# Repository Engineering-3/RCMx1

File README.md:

RCMx1
========================

This is an interface board for the RCM Control Stack that accommodates inputs (sensors) and outputs (motors, servos, LEDs) and communication through UART, SPI and I2C. Please see [Engineering3](http://engineering3.org/) for more information on the complete RCM Control Stack project.

Repository Contents
-------------------

* **/board** Eagle schematic/board files, gerbers, BOM
* **/firmware** Microcontroller firmware build files

Version History
---------------
* [RCMx1 Board v03](https://github.com/Engineering-3/RCMx1/tree/master/board/RCMx1_v03) First public hardware version - version 3 
* [RCMx1 Firmware v07](https://github.com/Engineering-3/RCMx1/tree/master/firmware) First public firmware version - version 7

License Information
-------------------
Hardware is released under [Solderpad Hardware License v0.51](http://solderpad.org/licenses/SHL-0.51/).
Firmware is released under [GNU GPL v2](http://www.gnu.org/licenses/old-licenses/gpl-2.0.html).
Distributed as-is; no warranty is given.

Getting Started Help
--------------------
Follow the [RCMx1 User Guide](https://github.com/Engineering-3/RCMx1/blob/master/firmware/docs/RCMx1%20User%20Guide.doc) here in the repo.

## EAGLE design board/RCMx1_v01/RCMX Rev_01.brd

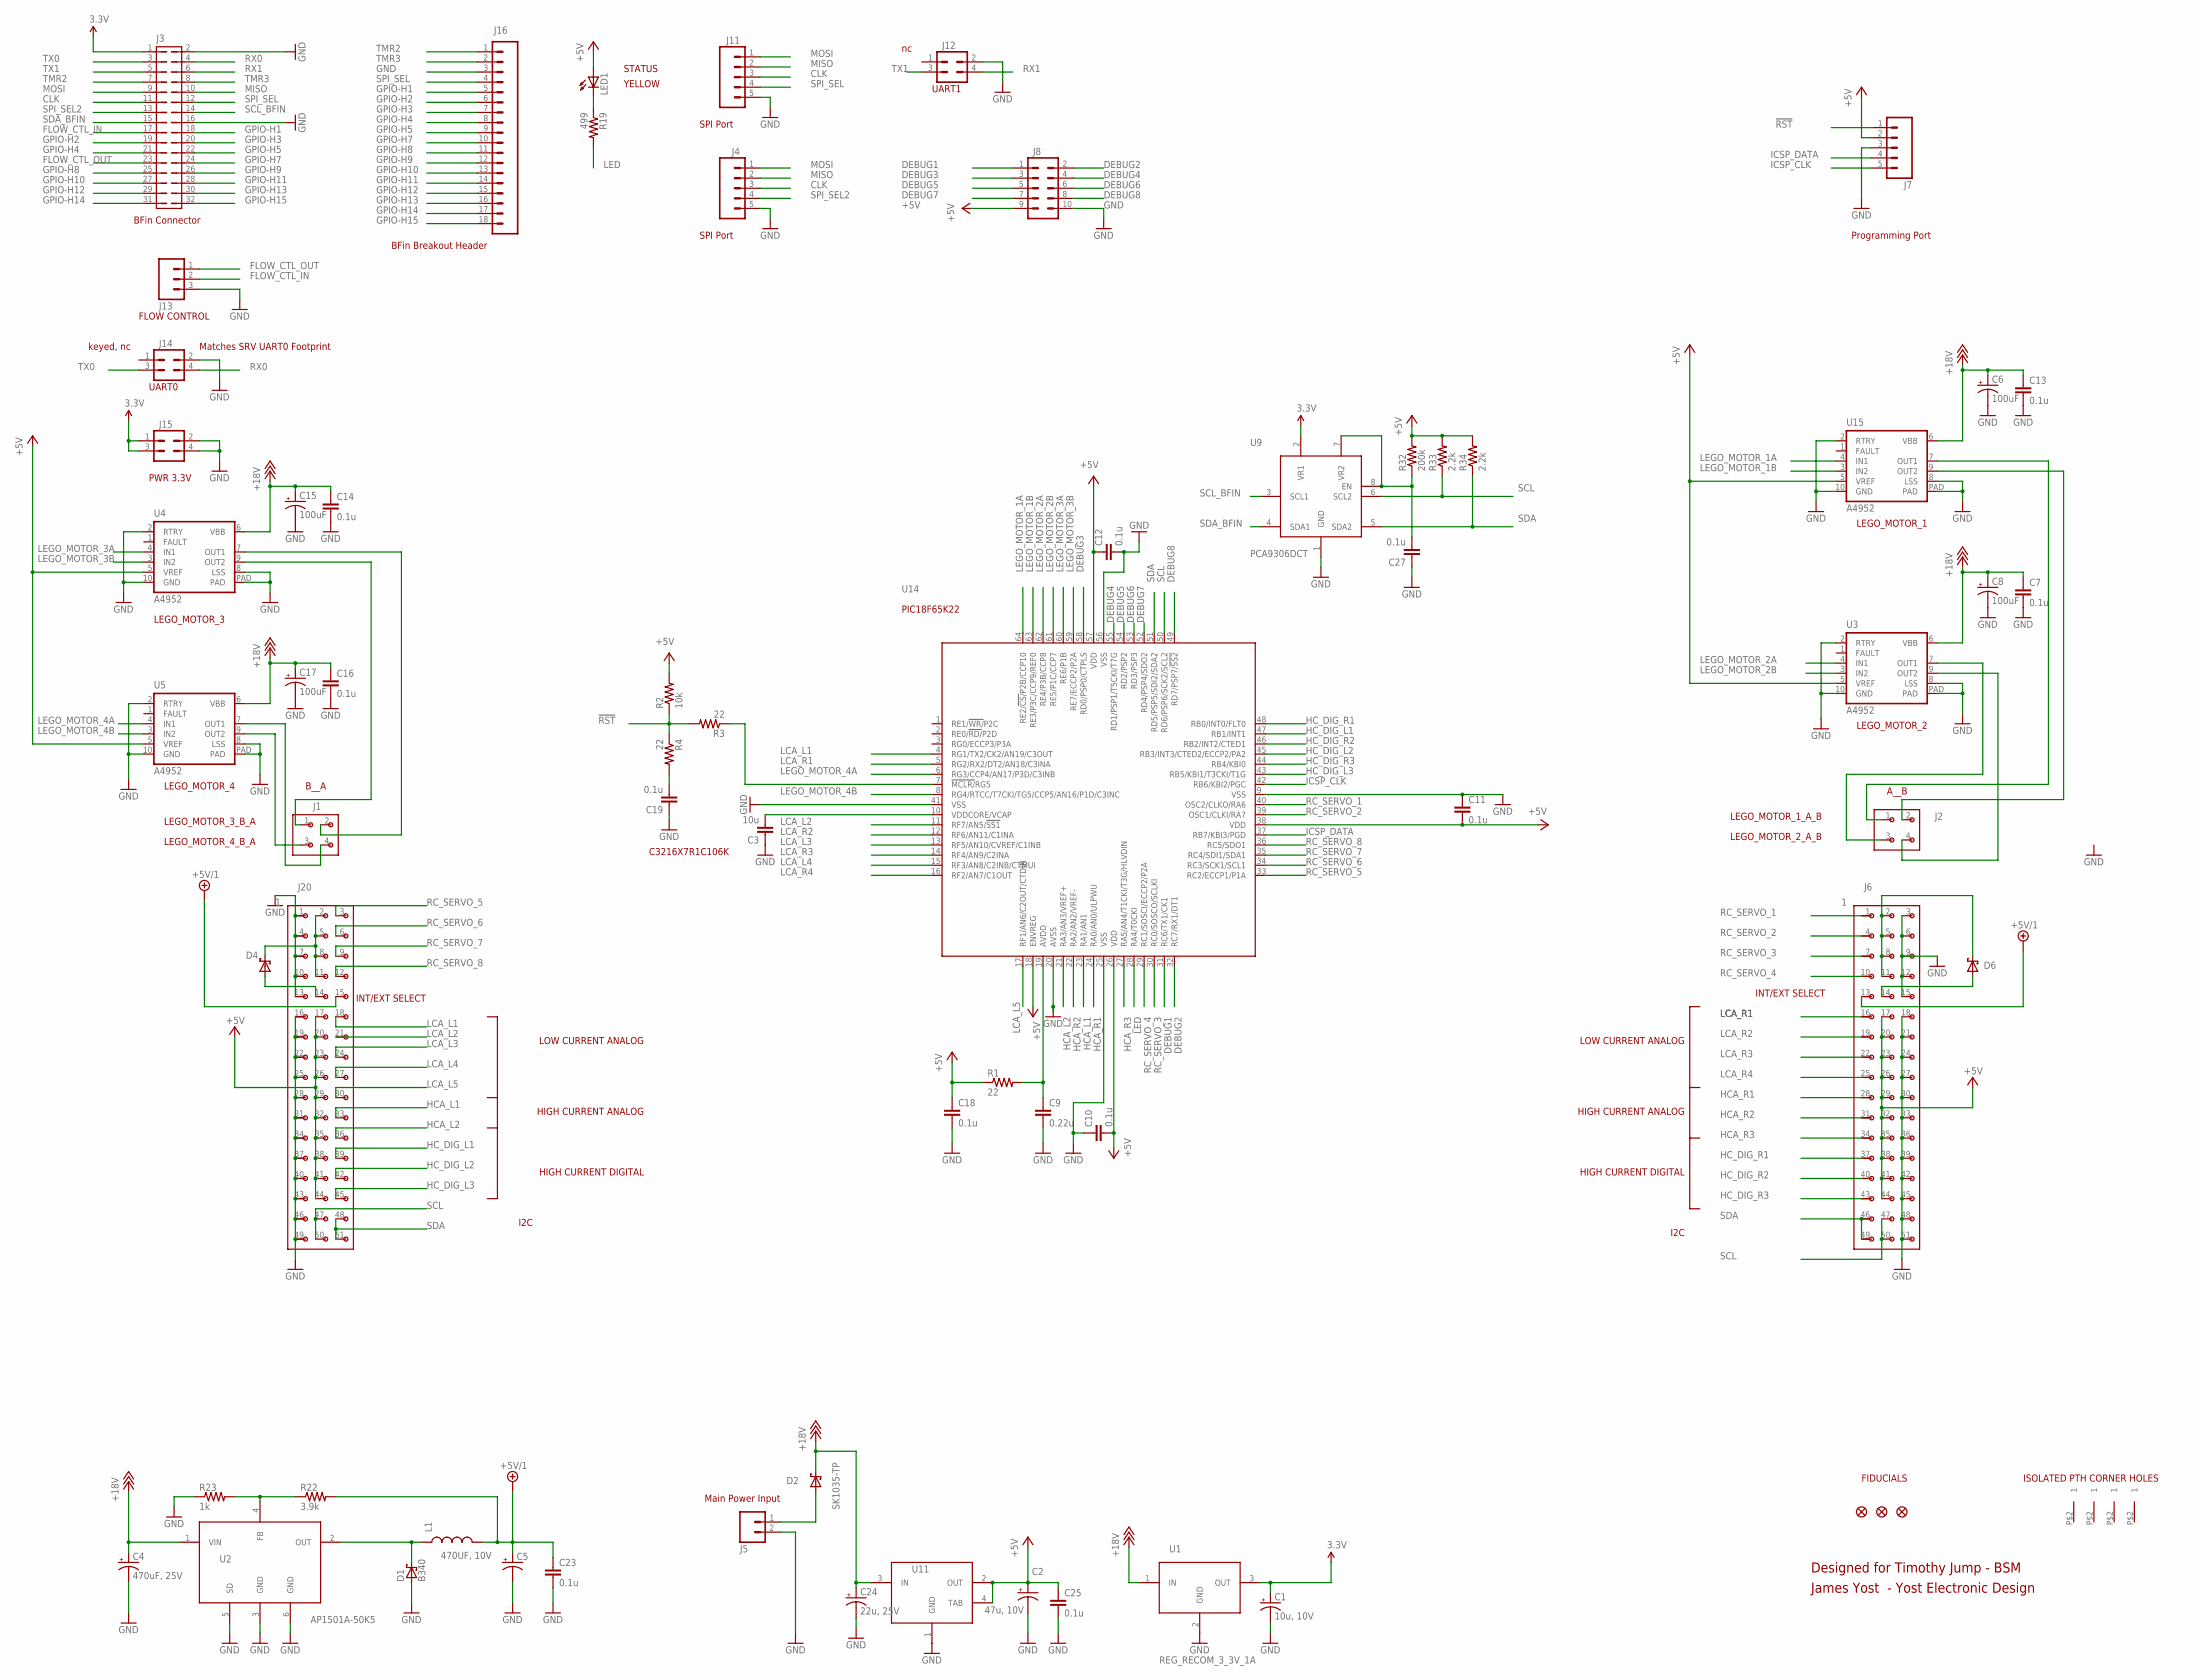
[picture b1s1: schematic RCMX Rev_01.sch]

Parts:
C1: 10u, 10V; EIA3216
C2: 47u, 10V; CAP1210_POL
C3: 10u; 1206
C4: 470uF, 25V; PANASONIC_G
C5: 470UF, 10V; PANASONIC_F
C6, C8, C15, C17: 100uF; PANASONIC_D
C7, C10, C11, C12, C13, C14, C16, C18, C19, C23, C25, C27: 0.1u; 0805
C9: 0.22u; 0805
C24: 22u, 25V; CAP1210_POL
D1: B340; SMA_DO214AC
D2, D4, D6: SK1035-TP; DO214AB
J1, J2: CON_2X2_0_100
J3: CON_2X16_0_100
J4, J7, J11: M05PTH; 1X05
J5: M02NG; 1X02
J6, J20: CON_3X17_0_100
J8: M05X2PTH; AVR_ICSP
J12, J14, J15: CON2X2
J13: M03PTH; 1X03
J16: CON1X18
L1: IND_47UH_COILTRONICS_2_95A; IND_PADS_SMT
LED1: LEDCHIP-LED0805; CHIP-LED0805
R1, R3, R4: 22; 0805
R2: 10k; 0805
R19: 499; 0805
R22: 3.9k; 0805
R23: 1k; 0805
R32: 200k; 0805
R33, R34: 2.2k; 0805
U1: REG_RECOM_3_3V_1A
U2: AP1501A-50K5; TO263-5
U3, U4, U5, U15: A4952; MSOP10_W_THERMAL_PAD
U9: PCA9306DCT; TEST08
U11: TLV1117-5; SOT223
U14: MICRO_C_PIC18F65K22; 64PIN_TQFP_10X10X1MM
U$1, U$2, U$7, U$8: GNDPAD
U$3, U$4, U$5: FIDUCIAL1X2.5; FIDUCIAL-1X2.5

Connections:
3.3V: C1.A (+), J3.1, J15.1, J15.3, U1.3 (OUT), U9.2 (VR1)
!RST: J7.1, R2.1, R3.2, R4.1
+5V: C2.1 (+), C10.2, C11.2, C12.1, C18.1, C25.1, J6.17, J6.20, J6.23, J6.26, J6.29, J6.32, J6.35, J6.38, J6.41, J6.44, J7.2, J8.9, J20.17, J20.20, J20.23, J20.26, J20.29, J20.32, J20.35, J20.38, J20.41, J20.44, LED1.A, R1.1, R2.2, R32.2, R33.2, R34.2, U3.5 (VREF), U4.5 (VREF), U5.5 (VREF), U11.2 (OUT), U11.4 (TAB), U14.18 (ENVREG), U14.26 (VDD), U14.38 (VDD), U14.57 (VDD), U15.5 (VREF)
+5V/1: C5.+, C23.1, J6.13, J20.15, L1.2, R22.2
+18V: C4.+, C6.+, C7.1, C8.+, C13.1, C14.1, C15.+, C16.1, C17.+, C24.1 (+), D2.1 (C), U1.1 (IN), U2.1 (VIN), U3.6 (VBB), U4.6 (VBB), U5.6 (VBB), U11.3 (IN), U15.6 (VBB)
CLK: J3.11, J4.3, J11.3
DEBUG1: J8.1, U14.31 (RC6/TX1/CK1)
DEBUG2: J8.2, U14.32 (RC7/RX1/DT1)
DEBUG3: J8.3, U14.58 (RD0/PSP0/CTPLS)
DEBUG4: J8.4, U14.55 (RD1/PSP1/T5CKI/T7G)
DEBUG5: J8.5, U14.54 (RD2/PSP2)
DEBUG6: J8.6, U14.53 (RD3/PSP3)
DEBUG7: J8.7, U14.52 (RD4/PSP4/SDO2)
DEBUG8: J8.8, U14.49 (RD7/PSP7/!SS2)
FLOW_CTL_IN: J3.17, J13.2
FLOW_CTL_OUT: J3.23, J13.1
GND: C1.C (-), C2.2 (-), C3.1, C4.-, C5.-, C6.-, C7.2, C8.-, C9.2, C10.1, C11.1, C12.2, C13.2, C14.2, C15.-, C16.2, C17.-, C18.2, C19.1, C23.2, C24.2 (-), C25.2, C27.1, D1.A, J3.2, J3.16, J4.5, J5.2, J6.3, J6.6, J6.9, J6.12, J6.15, J6.18, J6.21, J6.24, J6.27, J6.30, J6.33, J6.36, J6.39, J6.42, J6.45, J6.48, J6.51, J7.3, J8.10, J11.5, J12.2, J13.3, J14.2, J15.2, J15.4, J16.3, J20.1, J20.4, J20.7, J20.10, J20.13, J20.16, J20.19, J20.22, J20.25, J20.28, J20.31, J20.34, J20.37, J20.40, J20.43, J20.46, J20.49, R23.1, U1.2 (GND), U2.3 (GND), U2.5 (SD), U2.6 (GND), U3.2 (RTRY), U3.8 (LSS), U3.10 (GND), U3.PAD, U4.2 (RTRY), U4.8 (LSS), U4.10 (GND), U4.PAD, U5.2 (RTRY), U5.8 (LSS), U5.10 (GND), U5.PAD, U9.1 (GND), U11.1 (GND), U14.9 (VSS), U14.20 (AVSS), U14.25 (VSS), U14.41 (VSS), U14.56 (VSS), U15.2 (RTRY), U15.8 (LSS), U15.10 (GND), U15.PAD
GPIO-H1: J3.18, J16.5
GPIO-H2: J3.19, J16.6
GPIO-H3: J3.20, J16.7
GPIO-H4: J3.21, J16.8
GPIO-H5: J3.22, J16.9
GPIO-H7: J3.24, J16.10
GPIO-H8: J3.25, J16.11
GPIO-H9: J3.26, J16.12
GPIO-H10: J3.27, J16.13
GPIO-H11: J3.28, J16.14
GPIO-H12: J3.29, J16.15
GPIO-H13: J3.30, J16.16
GPIO-H14: J3.31, J16.17
GPIO-H15: J3.32, J16.18
HCA_L1: J20.33, U14.23 (RA1/AN1)
HCA_L2: J20.36, U14.21 (RA3/AN3/VREF+)
HCA_R1: J6.28, U14.24 (RA0/AN0/ULPWU)
HCA_R2: J6.31, U14.22 (RA2/AN2/VREF-)
HCA_R3: J6.34, U14.27 (RA5/AN4/T1CKI/T3G/HLVDIN)
HC_DIG_L1: J20.39, U14.47 (RB1/INT1)
HC_DIG_L2: J20.42, U14.45 (RB3/INT3/CTED2/ECCP2/PA2)
HC_DIG_L3: J20.45, U14.43 (RB5/KBI1/T3CKI/T1G)
HC_DIG_R1: J6.37, U14.48 (RB0/INT0/FLT0)
HC_DIG_R2: J6.40, U14.46 (RB2/INT2/CTED1)
HC_DIG_R3: J6.43, U14.44 (RB4/KBI0)
ICSP_CLK: J7.5, U14.42 (RB6/KBI2/PGC)
ICSP_DATA: J7.4, U14.37 (RB7/KBI3/PGD)
LCA_L1: J20.18, U14.4 (RG1/TX2/CK2/AN19/C3OUT)
LCA_L2: J20.21, U14.11 (RF7/AN5/!SS1)
LCA_L3: J20.24, U14.13 (RF5/AN10/CVREF/C1INB)
LCA_L4: J20.27, U14.15 (RF3/AN8/C2INB/CTMUI)
LCA_L5: J20.30, U14.17 (RF1/AN6/C2OUT/CTDIN)
LCA_R1: J6.16, U14.5 (RG2/RX2/DT2/AN18/C3INA)
LCA_R2: J6.19, U14.12 (RF6/AN11/C1INA)
LCA_R3: J6.22, U14.14 (RF4/AN9/C2INA)
LCA_R4: J6.25, U14.16 (RF2/AN7/C1OUT)
LED: R19.2, U14.28 (RA4/T0CKI)
LEGO_1A: J2.1, U15.7 (OUT1)
LEGO_1B: J2.2, U15.9 (OUT2)
LEGO_2A: J2.3, U3.7 (OUT1)
LEGO_2B: J2.4, U3.9 (OUT2)
LEGO_4A: J1.4, U5.7 (OUT1)
LEGO_4B: J1.3, U5.9 (OUT2)
LEGO_MOTOR_1A: U14.64 (RE2/!CS/!P2B/CCP10), U15.4 (IN1)
LEGO_MOTOR_1B: U14.63 (RE3/P3C/CCP9/REF0), U15.3 (IN2)
LEGO_MOTOR_2A: U3.4 (IN1), U14.62 (RE4/P3B/CCP8)
LEGO_MOTOR_2B: U3.3 (IN2), U14.61 (RE5/P1C/CCP7)
LEGO_MOTOR_3A: U4.4 (IN1), U14.60 (RE6/P1B)
LEGO_MOTOR_3B: U4.3 (IN2), U14.59 (RE7/ECCP2/P2A)
LEGO_MOTOR_4A: U5.4 (IN1), U14.6 (RG3/CCP4/AN17/P3D/C3INB)
LEGO_MOTOR_4B: U5.3 (IN2), U14.8 (RG4/RTCC/T7CKI/TG5/CCP5/AN16/P1D/C3INC)
MISO: J3.10, J4.2, J11.2
MOSI: J3.9, J4.1, J11.1
unnamed: D1.C, L1.1, U2.2 (OUT)
unnamed: R3.1, U14.7 (!MCLR/!RG5)
unnamed: D6.2 (A), J6.14
unnamed: D6.1 (C), J6.2, J6.5, J6.8, J6.11
unnamed: C19.2, R4.2
unnamed: D4.1 (C), J20.2, J20.5, J20.8, J20.11
unnamed: C9.1, R1.2, U14.19 (AVDD)
unnamed: D2.2 (A), J5.1
unnamed: J1.2, U4.7 (OUT1)
unnamed: J1.1, U4.9 (OUT2)
unnamed: R22.1, R23.2, U2.4 (FB)
unnamed: C3.2, U14.10 (VDDCORE/VCAP)
unnamed: D4.2 (A), J20.14
unnamed: C27.2, R32.1, U9.7 (VR2), U9.8 (EN)
unnamed: LED1.C, R19.1
RC_SERVO_1: J6.1, U14.40 (OSC2/CLKO/RA6)
RC_SERVO_2: J6.4, U14.39 (OSC1/CLKI/RA7)
RC_SERVO_3: J6.7, U14.30 (RC0/SOSCO/SCLKI)
RC_SERVO_4: J6.10, U14.29 (RC1/SOSCI/ECCP2/P2A)
RC_SERVO_5: J20.3, U14.33 (RC2/ECCP1/P1A)
RC_SERVO_6: J20.6, U14.34 (RC3/SCK1/SCL1)
RC_SERVO_7: J20.9, U14.35 (RC4/SDI1/SDA1)
RC_SERVO_8: J20.12, U14.36 (RC5/SDO1)
RX0: J3.4, J14.4
RX1: J3.6, J12.4
SCL: J6.47, J6.50, J20.47, J20.50, R33.1, U9.6 (SCL2), U14.50 (RD6/PSP6/SCK2/SCL2)
SCL_BFIN: J3.14, U9.3 (SCL1)
SDA: J6.46, J6.49, J20.48, J20.51, R34.1, U9.5 (SDA2), U14.51 (RD5/PSP5/SDI2/SDA2)
SDA_BFIN: J3.15, U9.4 (SDA1)
SPI_SEL: J3.12, J11.4, J16.4
SPI_SEL2: J3.13, J4.4
TMR2: J3.7, J16.1
TMR3: J3.8, J16.2
TX0: J3.3, J14.3
TX1: J3.5, J12.3

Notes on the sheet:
YELLOW
STATUS
BFin Connector
Programming Port
SPI Port
Main Power Input
UART1
FLOW CONTROL
PWR 3.3V
UART0
Matches SRV UART0 Footprint
keyed, nc
ISOLATED PTH CORNER HOLES
BFin Breakout Header
Designed for Timothy Jump - BSM
James Yost - Yost Electronic Design
INT/EXT SELECT
C3216X7R1C106K
LEGO_MOTOR_3
LEGO_MOTOR_4
LEGO_MOTOR_4_B_A
LEGO_MOTOR_3_B_A
B__A
LEGO_MOTOR_1
LEGO_MOTOR_2
LEGO_MOTOR_1_A_B
LEGO_MOTOR_2_A_B
A__B
LOW CURRENT ANALOG
HIGH CURRENT ANALOG
HIGH CURRENT DIGITAL
I2C
PIC18F65K22
FIDUCIALS

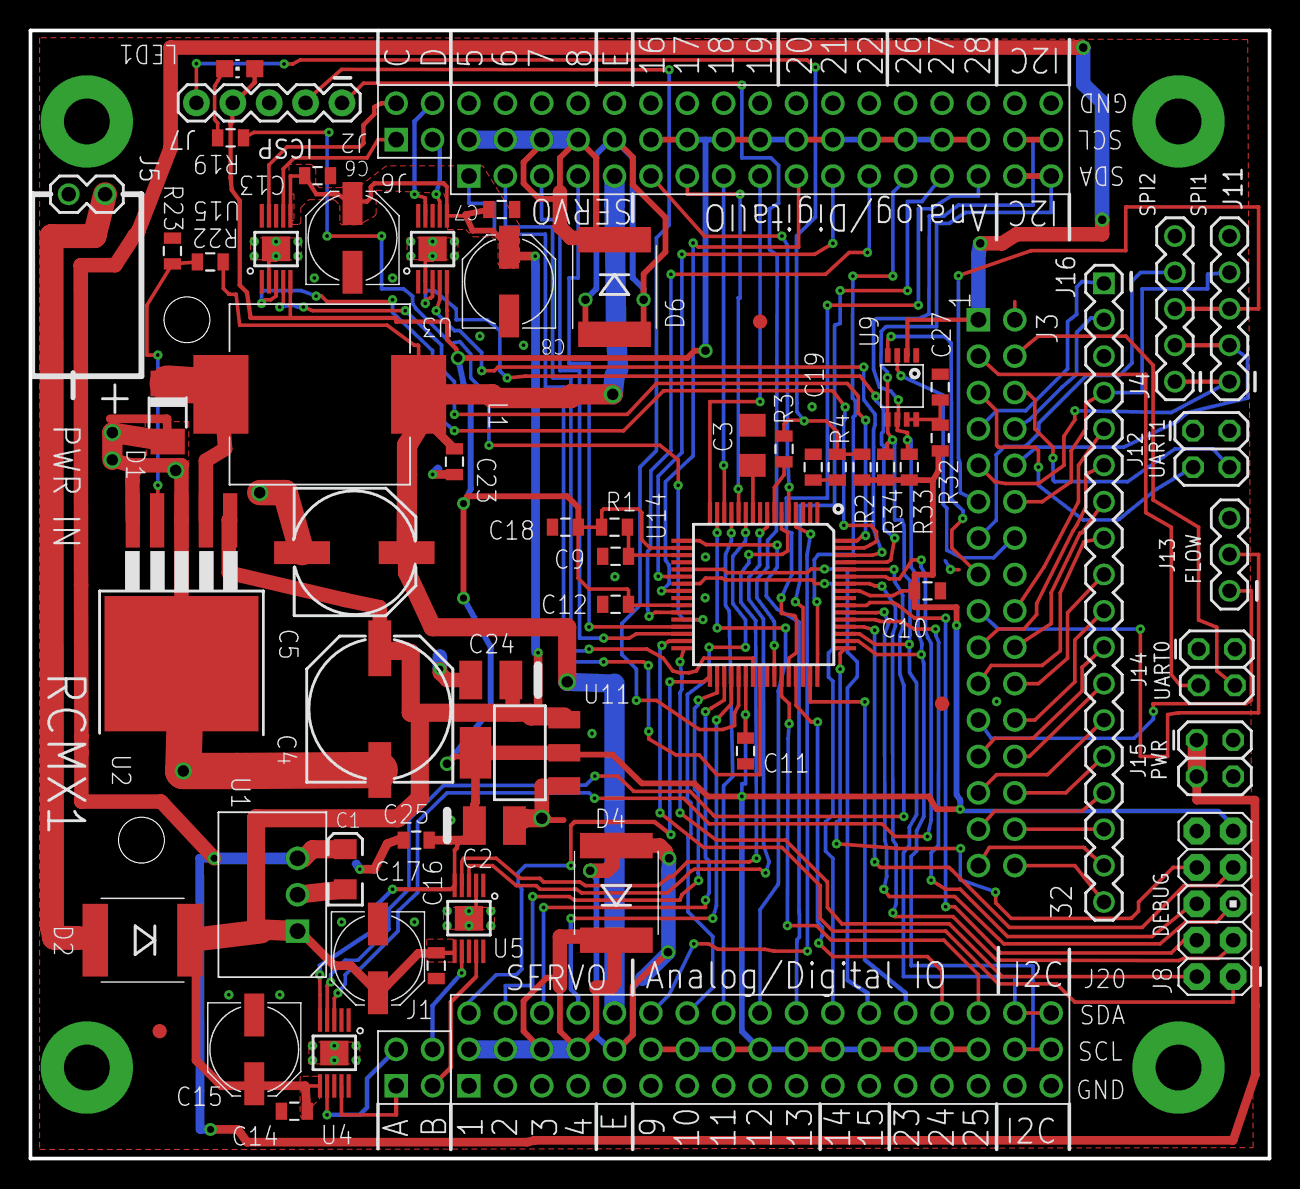
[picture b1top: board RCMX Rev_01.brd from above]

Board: 2 copper layers, 86.5 x 78.7 mm, 70 parts (0 on the bottom side), 105 nets.

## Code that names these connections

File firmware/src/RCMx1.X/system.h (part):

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#define DEFAULT_SAFETY_TIMEOUT_S    0

// For debug output bits
#define DEBUG1                      LATCbits.LATC6
#define DEBUG2                      LATCbits.LATC7
#define DEBUG3                      LATDbits.LATD0
#define DEBUG4                      LATDbits.LATD1
#define DEBUG5                      LATDbits.LATD2
#define DEBUG6                      LATDbits.LATD3
#define DEBUG7                      LATDbits.LATD4
#define DEBUG8                      LATDbits.LATD7

#define DEBUG1_TRIS                 TRISCbits.TRISC6
#define DEBUG2_TRIS                 TRISCbits.TRISC7
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#define DEBUG8_TRIS                 TRISDbits.TRISD7

// Define our pins
#define RCSERVO1_PIN                PORTCbits.RC2       // RC_SERVO_1
#define RCSERVO2_PIN                PORTCbits.RC3       // RC_SERVO_2
#define RCSERVO3_PIN                PORTCbits.RC4       // RC_SERVO_3
#define RCSERVO4_PIN                PORTCbits.RC5       // RC_SERVO_4
#define RCSERVO5_PIN                PORTAbits.RA6       // RC_SERVO_5
#define RCSERVO6_PIN                PORTAbits.RA7       // RC_SERVO_6
#define RCSERVO7_PIN                PORTCbits.RC0       // RC_SERVO_7
#define RCSERVO8_PIN                PORTCbits.RC1       // RC_SERVO_8

#define RCSERVO1_TRIS               TRISCbits.TRISC2    // RC_SERVO_1
#define RCSERVO2_TRIS               TRISCbits.TRISC3    // RC_SERVO_2
#define RCSERVO3_TRIS               TRISCbits.TRISC4    // RC_SERVO_3
#define RCSERVO4_TRIS               TRISCbits.TRISC5    // RC_SERVO_4
#define RCSERVO5_TRIS               TRISAbits.TRISA6    // RC_SERVO_5
#define RCSERVO6_TRIS               TRISAbits.TRISA7    // RC_SERVO_6
#define RCSERVO7_TRIS               TRISCbits.TRISC0    // RC_SERVO_7
#define RCSERVO8_TRIS               TRISCbits.TRISC1    // RC_SERVO_8

#define ANALOG1_PIN                 PORTGbits.RG1       // LCA_L1
#define ANALOG2_PIN                 PORTFbits.RF7       // LCA_L2
#define ANALOG3_PIN                 PORTFbits.RF5       // LCA_L3
#define ANALOG4_PIN                 PORTFbits.RF3       // LCA_L4
#define ANALOG5_PIN                 PORTFbits.RF1       // LCA_L5
#define ANALOG6_PIN                 PORTAbits.RA1       // HCA_L1
#define ANALOG7_PIN                 PORTAbits.RA3       // HCA_L2
#define ANALOG8_PIN                 PORTGbits.RG2       // LCA_R1
#define ANALOG9_PIN                 PORTFbits.RF6       // LCA_R2
#define ANALOG10_PIN                PORTFbits.RF4       // LCA_R3
#define ANALOG11_PIN                PORTFbits.RF2       // LCA_R4
#define ANALOG12_PIN                PORTAbits.RA0       // HCA_R1
#define ANALOG13_PIN                PORTAbits.RA2       // HCA_R2
#define ANALOG14_PIN                PORTAbits.RA5       // HCA_R3

#define ANALOG1_TRIS                TRISGbits.TRISG1    // LCA_L1
#define ANALOG2_TRIS                TRISFbits.TRISF7    // LCA_L2
#define ANALOG3_TRIS                TRISFbits.TRISF5    // LCA_L3
#define ANALOG4_TRIS                TRISFbits.TRISF3    // LCA_L4
#define ANALOG5_TRIS                TRISFbits.TRISF1    // LCA_L5
#define ANALOG6_TRIS                TRISAbits.TRISA1    // HCA_L1
#define ANALOG7_TRIS                TRISAbits.TRISA3    // HCA_L2
#define ANALOG8_TRIS                TRISGbits.TRISG2    // LCA_R1
#define ANALOG9_TRIS                TRISFbits.TRISF6    // LCA_R2
#define ANALOG10_TRIS               TRISFbits.TRISF4    // LCA_R3
#define ANALOG11_TRIS               TRISFbits.TRISF2    // LCA_R4
#define ANALOG12_TRIS               TRISAbits.TRISA0    // HCA_R1
#define ANALOG13_TRIS               TRISAbits.TRISA2    // HCA_R2
#define ANALOG14_TRIS               TRISAbits.TRISA5    // HCA_R3

#define ANALOG1_ENABLE              ANCON2bits.ANSEL19  // LCA_L1
#define ANALOG2_ENABLE              ANCON0bits.ANSEL5   // LCA_L2
#define ANALOG3_ENABLE              ANCON1bits.ANSEL10  // LCA_L3
#define ANALOG4_ENABLE              ANCON1bits.ANSEL8   // LCA_L4
#define ANALOG5_ENABLE              ANCON0bits.ANSEL6   // LCA_L5
#define ANALOG6_ENABLE              ANCON0bits.ANSEL1   // HCA_L1
#define ANALOG7_ENABLE              ANCON0bits.ANSEL3   // HCA_L2
#define ANALOG8_ENABLE              ANCON2bits.ANSEL18  // LCA_R1
#define ANALOG9_ENABLE              ANCON1bits.ANSEL11  // LCA_R2
#define ANALOG10_ENABLE             ANCON1bits.ANSEL9   // LCA_R3
#define ANALOG11_ENABLE             ANCON0bits.ANSEL7   // LCA_R4
#define ANALOG12_ENABLE             ANCON0bits.ANSEL0   // HCA_R1
#define ANALOG13_ENABLE             ANCON0bits.ANSEL2   // HCA_R2
#define ANALOG14_ENABLE             ANCON0bits.ANSEL4   // HCA_R3

// Maps GPIO numbers 1 through 6 to actual positions within PORTB pins
#define GPIO1_BIT                   1<<1
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
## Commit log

2015-02-14 Initial checkin of files from Logic.
2015-02-14 Created new v3 version of the board, added new copyright, license, OSHW, etc. to schematic and board.
2015-02-16 Fixed some file locations to make things clearer.
2015-02-17 Moved firmware files from other repo here.
2015-02-19 Added readme.
2015-02-20 Updated link to RCMx1 user guide.
2015-02-26 Updated RCMx1_Commands doc with the following changes: * GPIO and Analog ports now have 0 as input and 1 as output for data direction bits * Clarified what's working and what's not tested with analog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
2015-03-05 Version 0x08 of RCMx1 firmware. * Updated Command document to reflect actual code - marked sections as not implemented and set default values to be 0x00 * Updated firmware to match command document, 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
2015-03-05 Added 0x08 RCMx1 firmware hex file.
2015-03-11 Fixed some minor consistency issues in the RCMx1 Commands document.
2015-03-12 New version 0x09 of RCMx1 firmware. Implements changes to register 0x21, as per updated RCMx1_Commands.txt document Also marked saftey timeouts as unimplemented.
2015-03-19 Tim found a bug with H-Bridge motor output A (it acted backwards from the other 3). This has now been fixed and tested. Bumped version number to 0x0A.
2015-03-22 Now at version 0x0B. Fixed a bug where we were using inverted bits to initialize the analog enable bits.
2015-03-22 Adding the latest versions in.
2015-03-31 Version 0x0C - changed operation of analog value registers (0xB1 - 0xBE) so that they read zero if their bit is set in register 0xA4.
2015-03-31 Version 0x0C.
2015-04-18 Version 0x0D. Got all of the RC Servo 'filter' functions working properly (I think). Needs more testing by Tim. Updated commands.txt document to reflect RC servo filter implementation.
2015-04-19 Version 0x0E : Re-wrote safety timeout system
    We now have a single safety timeout value register, and any read/write from the whole RCMx1 board will reset the timer. Updated commands.txt to reflect this.
2015-05-09 New version 0x0F: Fixed bug with RC Servo channels - in several previous versions (at least 0x0D and 0x0E) if you ever sent 0x00 to a RC servo channel, it would stay off forever even if you sent vali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
2015-07-28 Fixed bug reading analog input pin 10 as digital input. Updated documentation (clarified analog input GPIO register details, and removed extra safety timeout registers that are no longer used. Create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
2015-08-01 Version 0x11 released: Instead of shutting off RC servo outputs when safety timeout expires, we now 'center' them at 1.5ms pulses (0x80)
2015-08-02 Version 0x12 : Changed safety timeout to ONLY be reset with read/write of register 0x0F. This prevents streaming sensors from LabView from constantly resetting the safety timeout value.
2015-08-03 Version 0x13: Changed Safety Timeout so that when it trips, we set all DC motor outputs to 'brake' (i.e. 0x80) rather than 'coast' (0x00).
2016-02-29 Created version 04 of RCMx1 board - silk screen layer changes only, no component, schematic, or other board changes.
2016-02-29 Rotated board name on top silk layer 180 degrees.
2016-03-01 Added RCMx1 Rev_04 gerbers (OSH Park CAM)
2016-03-05 Updated BOM for v04 : updated connectors to be gold plated.
2016-07-31 Removed text in bottom copper layer
2016-07-31 * Created gerbers from updated Eagle board files
2016-08-01 Added board build readme.
2016-09-05 Added PDFs of schematic and board layout for rev 04
2016-11-30 Created RCMx1 rev 05 - fixed pin 1 silk screen designator for J7
2018-03-20 Fixed spelling on bottom silk layer.
2019-05-12 Updated pin chart to reflect unused timer channel gate pin and four interrupt pins.
2019-05-20 Moved docs file
2020-01-17 Updated RCMx1_Commands.txt with detailed timing information about the RC servo outputs.

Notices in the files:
firmware/src/RCMx1.X/system.h:
Copyright Engineering^3 2015
modify it under the terms of the GNU General Public License
parts and their libraries:
SparkFun-Connectors: Licensing: CC v3.0 Share-Alike You are welcome to use this library for commercial purposes.
